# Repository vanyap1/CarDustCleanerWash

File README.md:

# CarDustCleanerWash
CarDustCleanerWash

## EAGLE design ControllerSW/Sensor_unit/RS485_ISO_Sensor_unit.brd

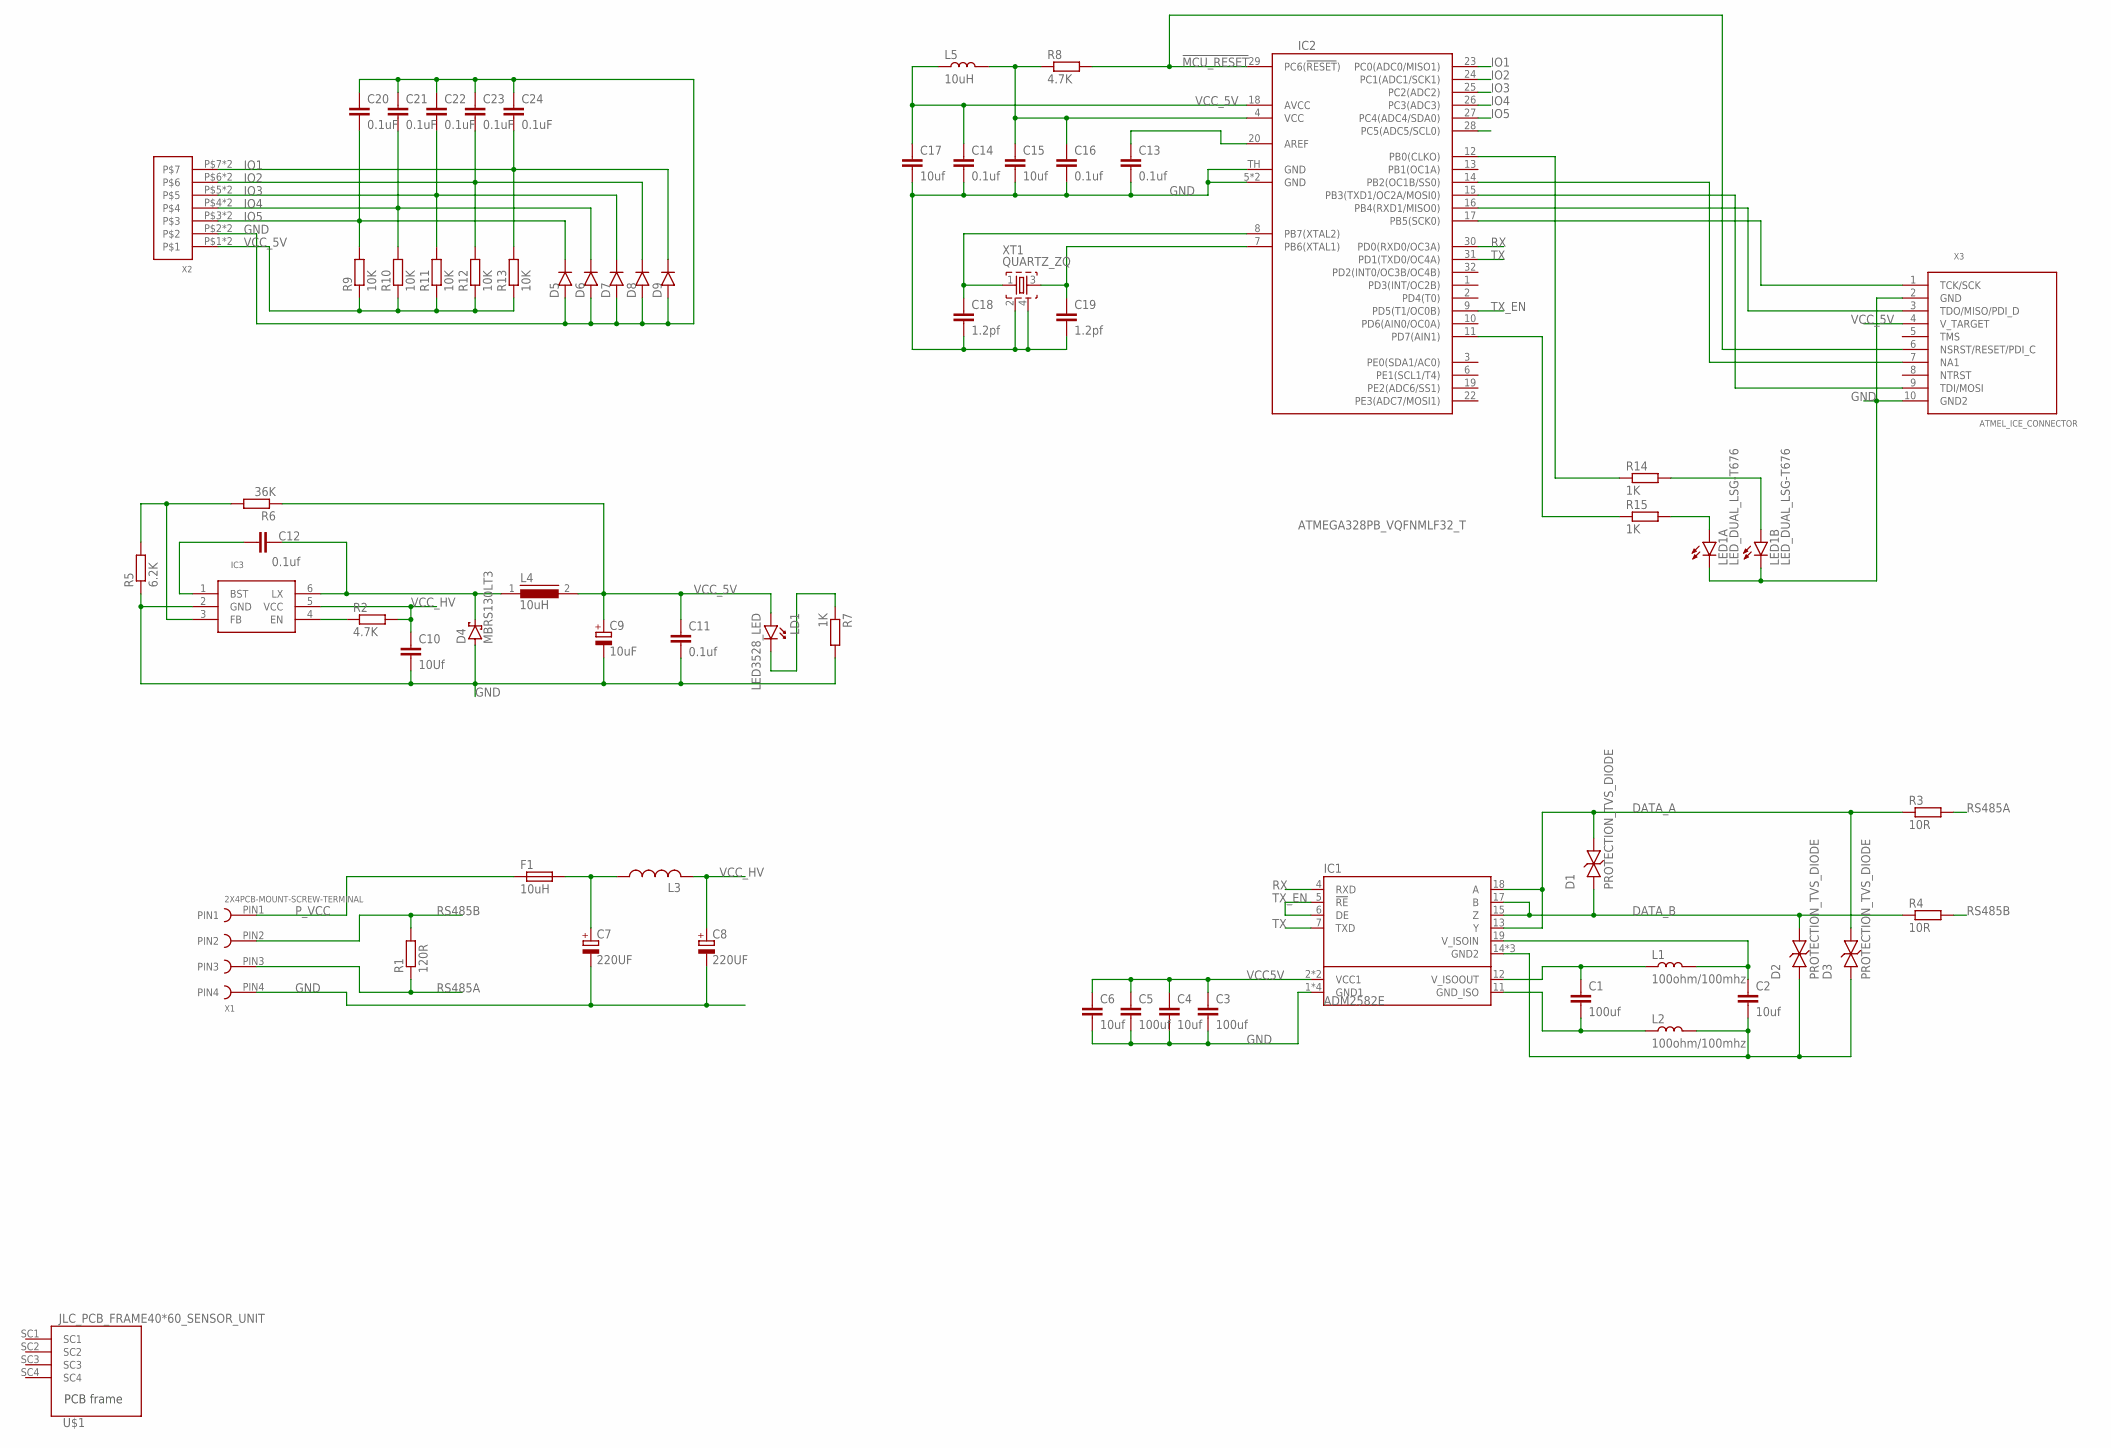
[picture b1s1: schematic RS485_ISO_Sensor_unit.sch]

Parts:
C1, C3, C5: 100uf; 0603
C2, C4, C6: 10uf; 0603
C7, C8: 220UF; 3.6MM
C9: 10uF; D/7343-31R
C10: 10Uf; 1206
C11, C12, C13, C14, C16: 0.1uf; 0603
C15, C17: 10uf; 3528
C18, C19: 1.2pf; 0603
C20, C21, C22, C23, C24: 0.1uF; 0603
D1, D2, D3: PROTECTION_TVS_DIODE; SMA403D
D4: MBRS130LT3; SMB
D5, D6, D7, D8, D9: L1N4148WT1GSOD123_GALILE0_SMALL; SOD-123_MINI-SMA
F1: 10uH; SMD_2410_FUSE_NOK
IC1: ADM2582E; SO20L
IC2: ATMEGA328PB_VQFNMLF32_T; MLF32-TH
IC3: BD9G101G_SOT23(6); SOT-23(6)
L1, L2: 100ohm/100mhz; 0805
L3: L-US0207/2V; 0207/2V
L4: 10uH; DR74
L5: 10uH; 0805
LD1: LED3528_LED; 3528
LED1: LED_DUAL_LSG-T676; P-LCC4-0
R1: 120R; 0204/5
R2, R8: 4.7K; 0603
R3, R4: 10R; 1206
R5: 6.2K; 0603
R6: 36K; 0603
R7, R14, R15: 1K; 0603
R9, R10, R11, R12, R13: 10K; 0603
U$1: JLC_PCB_FRAME40*60_SENSOR_UNIT; 40X60_SENSOR_UNIT
X1: 2X4PCB-MOUNT-SCREW-TERMINAL
X2: WAGO250_X7; WAGO250_FP_7X
X3: ATMEL_ICE_CONNECTOR; MINI10P_SPI/JTAG/PDI
XT1: QUARTZ_ZQ; QUARTZ_3X3MM

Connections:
!MCU_RESET: IC2.29 (PC6(!RESET!)), R8.2, X3.6 (NSRST/RESET/PDI_C)
AREF: C13.1, IC2.20 (AREF)
AVCC: C14.1, C17.M (1), IC2.18 (AVCC), L5.1
DATA_A: D1.P$2 (C), D3.P$2 (C), IC1.13 (Y), IC1.18 (A), R3.1
DATA_B: D1.P$1 (A), D2.P$2 (C), IC1.15 (Z), IC1.17 (B), R4.1
GND: C3.2, C4.2, C5.2, C6.2, C7.P$1 (-), C8.P$1 (-), C9.-, C10.2, C11.2, C13.2, C14.2, C15.P (2), C16.2, C17.P (2), C18.2, C19.2, C20.1, C21.1, C22.1, C23.1, C24.1, D4.A, D5.A, D6.A, D7.A, D8.A, D9.A, IC1.1 (GND1), IC1.3 (GND1), IC1.9 (GND1), IC1.10 (GND1), IC2.5 (GND), IC2.21 (GND), IC2.TH (GND), IC3.2 (GND), LED1.1 (C), LED1.3 (C), R5.1, R7.2, X1.PIN4, X2.P$2, X2.U$2, X3.2 (GND), X3.10 (GND2), XT1.2, XT1.4
GND2: C2.2, D2.P$1 (A), D3.P$1 (A), IC1.14 (GND2), IC1.16 (GND2), IC1.20 (GND2), L2.2
IO1: C24.2, D9.C, IC2.23 (PC0(ADC0/MISO1)), R13.2, X2.P$7, X2.U$7
IO2: C23.2, D8.C, IC2.24 (PC1(ADC1/SCK1)), R12.2, X2.P$6, X2.U$6
IO3: C22.2, D7.C, IC2.25 (PC2(ADC2)), R11.2, X2.P$5, X2.U$5
IO4: C21.2, D6.C, IC2.26 (PC3(ADC3)), R10.2, X2.P$4, X2.U$4
IO5: C20.2, D5.C, IC2.27 (PC4(ADC4/SDA0)), R9.2, X2.P$3, X2.U$3
unnamed: C7.P$2 (+), F1.P$2 (2), L3.1
unnamed: IC3.4 (EN), R2.1
unnamed: C1.1, IC1.12 (V_ISOOUT), L1.1
unnamed: C2.1, IC1.19 (V_ISOIN), L1.2
unnamed: C1.2, IC1.11 (GND_ISO), L2.1
unnamed: C12.1, IC3.1 (BST)
unnamed: IC3.3 (FB), R5.2, R6.2
unnamed: C12.2, D4.C, IC3.6 (LX), L4.1
unnamed: LED1.2 (A), R15.2
unnamed: LED1.4 (A), R14.2
unnamed: IC2.12 (PB0(CLKO)), R14.1
unnamed: LD1.M (K), R7.1
unnamed: IC2.17 (PB5(SCK0)), X3.1 (TCK/SCK)
unnamed: IC2.16 (PB4(RXD1/MISO0)), X3.3 (TDO/MISO/PDI_D)
unnamed: IC2.15 (PB3(TXD1/OC2A/MOSI0)), X3.9 (TDI/MOSI)
unnamed: IC2.11 (PD7(AIN1)), R15.1
unnamed: IC2.14 (PB2(OC1B/SS0)), X3.7 (NA1)
unnamed: C18.1, IC2.8 (PB7(XTAL2)), XT1.1
unnamed: C19.1, IC2.7 (PB6(XTAL1)), XT1.3
P_VCC: F1.P$1 (1), X1.PIN1
RS485A: R1.1, R3.2, X1.PIN3
RS485B: R1.2, R4.2, X1.PIN2
RX: IC1.4 (RXD), IC2.30 (PD0(RXD0/OC3A))
TX: IC1.7 (TXD), IC2.31 (PD1(TXD0/OC4A))
TX_EN: IC1.5 (!RE), IC1.6 (DE), IC2.9 (PD5(T1/OC0B))
VCC5V: C3.1, C4.1, C5.1, C6.1, IC1.2 (VCC1), IC1.8 (VCC1)
VCC_5V: C9.+, C11.1, C15.M (1), C16.1, IC2.4 (VCC), L4.2, L5.2, LD1.P (A), R6.1, R8.1, R9.1, R10.1, R11.1, R12.1, R13.1, X2.P$1, X2.U$1, X3.4 (V_TARGET)
VCC_HV: C8.P$2 (+), C10.1, IC3.5 (VCC), L3.2, R2.2

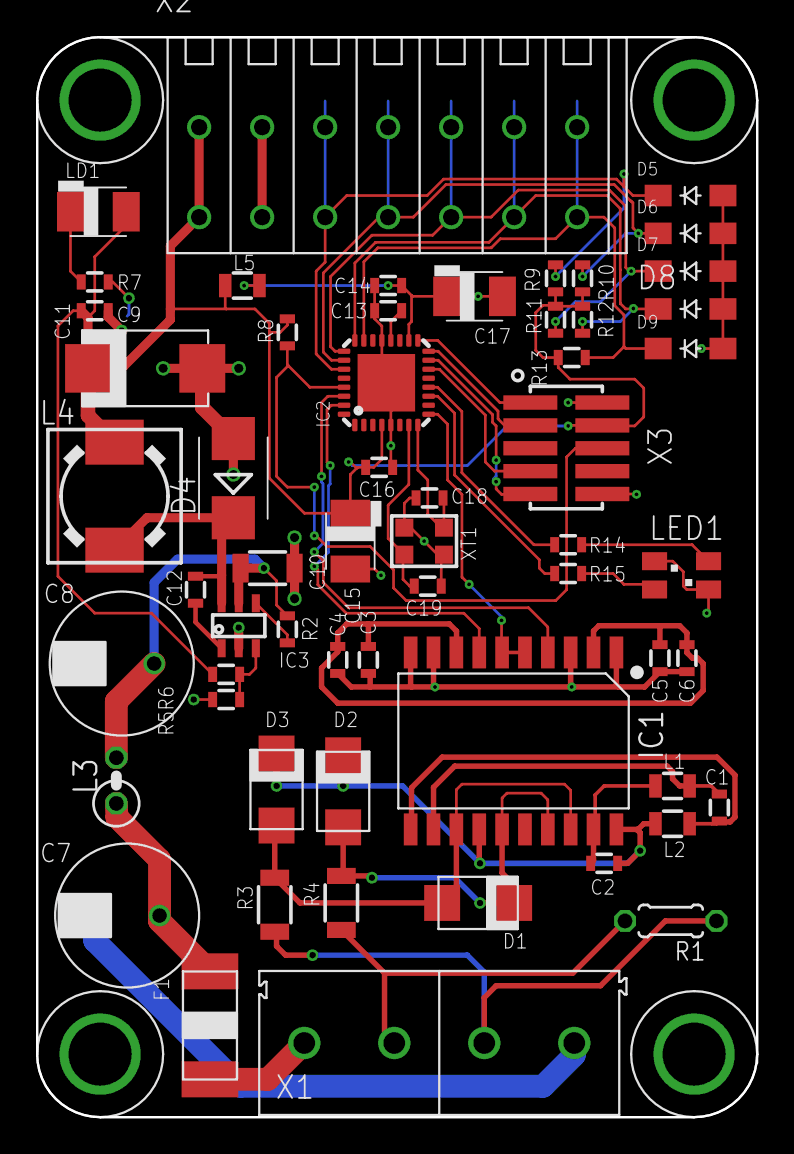
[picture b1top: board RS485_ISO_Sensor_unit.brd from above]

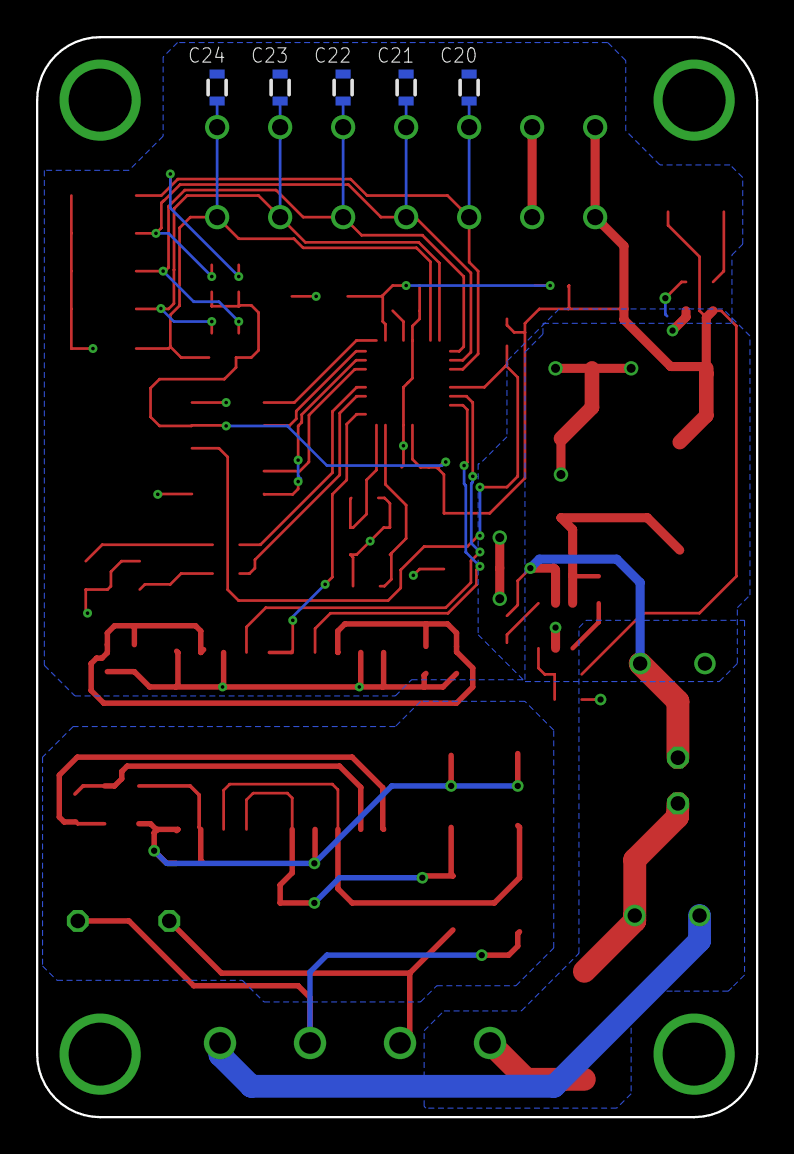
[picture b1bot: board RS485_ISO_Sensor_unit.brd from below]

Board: 2 copper layers, 40.0 x 60.0 mm, 64 parts (5 on the bottom side), 40 nets.

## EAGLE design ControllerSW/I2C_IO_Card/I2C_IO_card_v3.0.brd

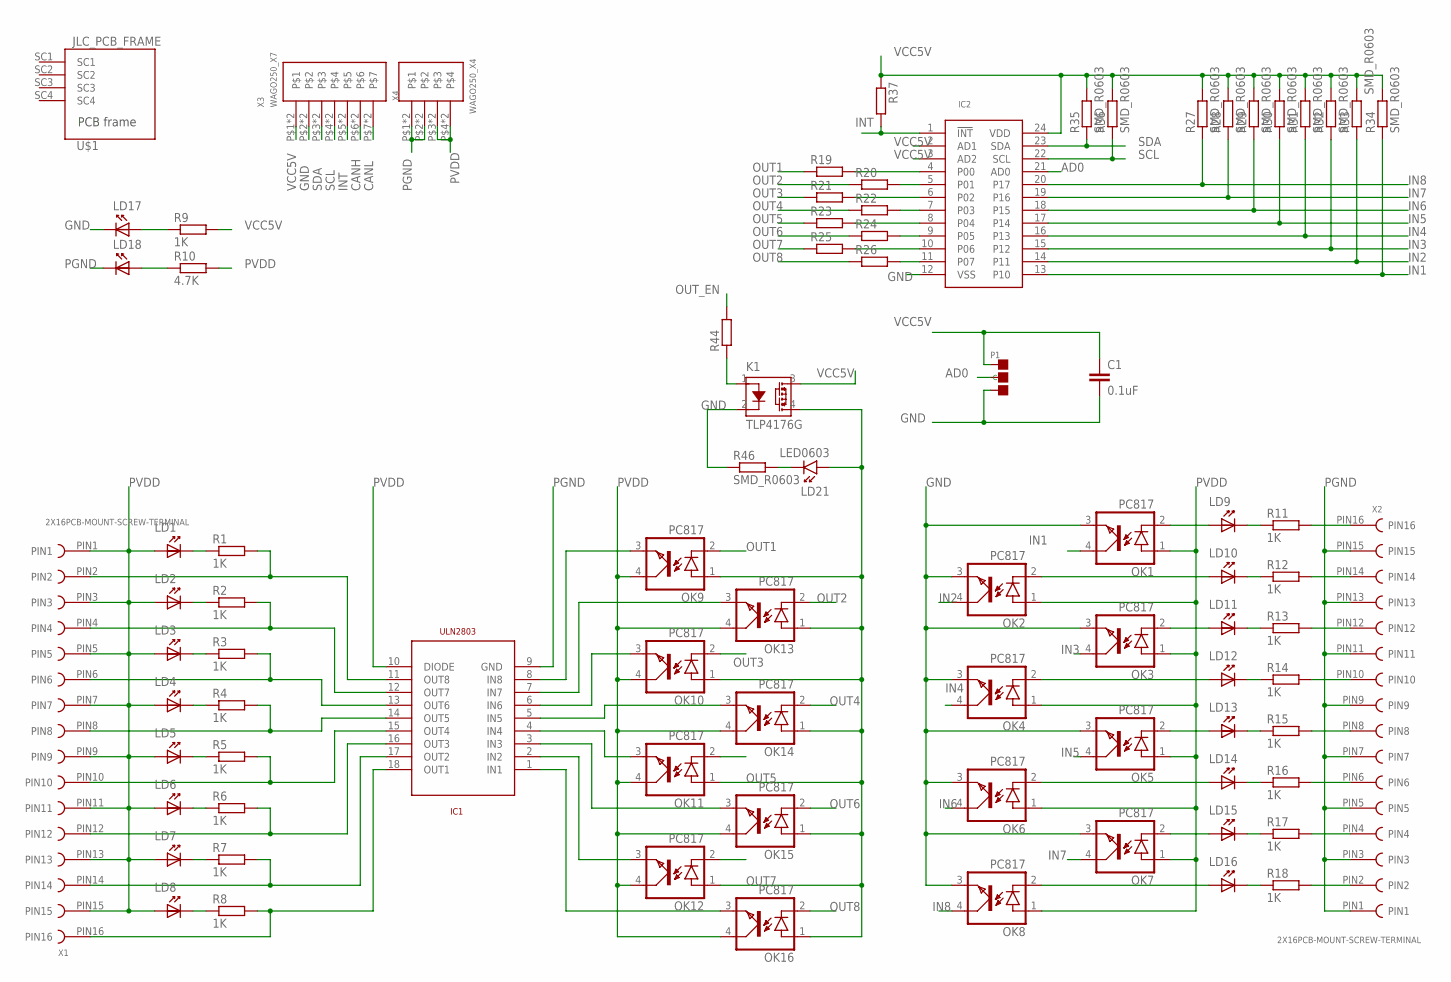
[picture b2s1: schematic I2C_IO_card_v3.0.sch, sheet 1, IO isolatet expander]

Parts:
C1: 0.1uF; C0603K
IC1: ULN2803; SO18L
IC2: PCA9675_TSSOP24; SOP65P640X110-24N
K1: TLP4176G; SOP04
LD1, LD2, LD3, LD4, LD5, LD6, LD7, LD8, LD9, LD10, LD11, LD12, LD13, LD14, LD15, LD16, LD17, LD18: LED; LED_RADIAL_3MM
LD21: LED0603; 0603_P
OK1, OK2, OK3, OK4, OK5, OK6, OK7, OK8, OK9, OK10, OK11, OK12, OK13, OK14, OK15, OK16: PC817; DIL04
P1: PAD-JUMPER-3P-40*40; 3P-SMD-4.1X1.5
R1, R2, R3, R4, R5, R6, R7, R8, R9, R11, R12, R13, R14, R15, R16, R17, R18: 1K; R0603
R10: 4.7K; R0603
R19, R20, R21, R22, R23, R24, R25, R26, R27, R28, R29, R30, R31, R32, R33, R34, R35, R36, R44, R46: SMD_R0603; 0603
R37: R-EU_RO603K; R0603K
U$1: JLC_PCB_FRAME; 80X100_PCB_FRAME
X1, X2: 2X16PCB-MOUNT-SCREW-TERMINAL
X3: WAGO250_X7; WAGO250_FP_7X
X4: WAGO250_X4; WAGO250_FP_4X

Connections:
AD0: IC2.21 (AD0), P1.MM (C)
CANH: X3.P$6, X3.U$6; also elsewhere on the board
CANL: X3.P$7, X3.U$7; also elsewhere on the board
GND: C1.2, IC2.12 (VSS), K1.2 (K), LD17.K, OK1.3 (EMIT), OK2.3 (EMIT), OK3.3 (EMIT), OK4.3 (EMIT), OK5.3 (EMIT), OK6.3 (EMIT), OK7.3 (EMIT), OK8.3 (EMIT), P1.11 (R), R46.1, X3.P$2, X3.U$2; also elsewhere on the board
IN1: IC2.13 (P10), OK1.4 (COL), R34.1; also elsewhere on the board
IN2: IC2.14 (P11), OK2.4 (COL), R33.1
IN3: IC2.15 (P12), OK3.4 (COL), R32.1
IN4: IC2.16 (P13), OK4.4 (COL), R31.1
IN5: IC2.17 (P14), OK5.4 (COL), R30.1
IN6: IC2.18 (P15), OK6.4 (COL), R29.1
IN7: IC2.19 (P16), OK7.4 (COL), R28.1
IN8: IC2.20 (P17), OK8.4 (COL), R27.1
INT: IC2.1 (!INT), R37.2, X3.P$5, X3.U$5; also elsewhere on the board
unnamed: LD1.K, R1.1
unnamed: LD2.K, R2.1
unnamed: LD3.K, R3.1
unnamed: LD4.K, R4.1
unnamed: LD5.K, R5.1
unnamed: LD6.K, R6.1
unnamed: LD7.K, R7.1
unnamed: LD8.K, R8.1
unnamed: IC1.18 (OUT1), R8.2, X1.PIN16
unnamed: IC1.17 (OUT2), R7.2, X1.PIN14
unnamed: IC1.16 (OUT3), R6.2, X1.PIN12
unnamed: IC1.15 (OUT4), R5.2, X1.PIN10
unnamed: IC1.14 (OUT5), R4.2, X1.PIN8
unnamed: IC1.13 (OUT6), R3.2, X1.PIN6
unnamed: IC1.12 (OUT7), R2.2, X1.PIN4
unnamed: IC1.11 (OUT8), R1.2, X1.PIN2
unnamed: LD17.A, R9.1
unnamed: LD18.A, R10.1
unnamed: R18.2, X2.PIN2
unnamed: R17.2, X2.PIN4
unnamed: R16.2, X2.PIN6
unnamed: R15.2, X2.PIN8
unnamed: R14.2, X2.PIN10
unnamed: R13.2, X2.PIN12
unnamed: R12.2, X2.PIN14
unnamed: R11.2, X2.PIN16
unnamed: LD9.K, R11.1
unnamed: LD10.K, R12.1
unnamed: LD11.K, R13.1
unnamed: LD12.K, R14.1
unnamed: LD13.K, R15.1
unnamed: LD14.K, R16.1
unnamed: LD15.K, R17.1
unnamed: LD16.K, R18.1
unnamed: LD9.A, OK1.2 (C)
unnamed: LD11.A, OK3.2 (C)
unnamed: LD13.A, OK5.2 (C)
unnamed: LD15.A, OK7.2 (C)
unnamed: LD16.A, OK8.2 (C)
unnamed: LD14.A, OK6.2 (C)
unnamed: LD12.A, OK4.2 (C)
unnamed: LD10.A, OK2.2 (C)
unnamed: IC2.4 (P00), R19.2
unnamed: IC1.8 (IN8), OK9.3 (EMIT)
unnamed: IC1.7 (IN7), OK13.3 (EMIT)
unnamed: IC1.6 (IN6), OK10.3 (EMIT)
unnamed: IC1.5 (IN5), OK14.3 (EMIT)
unnamed: IC1.4 (IN4), OK11.3 (EMIT)
unnamed: IC1.3 (IN3), OK15.3 (EMIT)
unnamed: IC1.2 (IN2), OK12.3 (EMIT)
unnamed: IC1.1 (IN1), OK16.3 (EMIT)
unnamed: IC2.5 (P01), R20.2
unnamed: IC2.6 (P02), R21.2
unnamed: IC2.7 (P03), R22.2
unnamed: IC2.8 (P04), R23.2
unnamed: IC2.9 (P05), R24.2
unnamed: IC2.10 (P06), R25.2
unnamed: IC2.11 (P07), R26.2
unnamed: K1.4 (DS2), LD21.2 (A), OK9.1 (A), OK10.1 (A), OK11.1 (A), OK12.1 (A), OK13.1 (A), OK14.1 (A), OK15.1 (A), OK16.1 (A)
unnamed: K1.1 (A), R44.1
unnamed: LD21.1 (K), R46.2
OUT1: OK9.2 (C), R19.1
OUT2: OK13.2 (C), R20.1
OUT3: OK10.2 (C), R21.1
OUT4: OK14.2 (C), R22.1
OUT5: OK11.2 (C), R23.1
OUT6: OK15.2 (C), R24.1
OUT7: OK12.2 (C), R25.1
OUT8: OK16.2 (C), R26.1
OUT_EN: R44.2; also elsewhere on the board
PGND: IC1.9 (GND), LD18.K, X2.PIN1, X2.PIN3, X2.PIN5, X2.PIN7, X2.PIN9, X2.PIN11, X2.PIN13, X2.PIN15, X4.P$1, X4.P$2, X4.U$1, X4.U$2; also elsewhere on the board
PVDD: IC1.10 (DIODE), LD1.A, LD2.A, LD3.A, LD4.A, LD5.A, LD6.A, LD7.A, LD8.A, OK1.1 (A), OK2.1 (A), OK3.1 (A), OK4.1 (A), OK5.1 (A), OK6.1 (A), OK7.1 (A), OK8.1 (A), OK9.4 (COL), OK10.4 (COL), OK11.4 (COL), OK12.4 (COL), OK13.4 (COL), OK14.4 (COL), OK15.4 (COL), OK16.4 (COL), R10.2, X1.PIN1, X1.PIN3, X1.PIN5, X1.PIN7, X1.PIN9, X1.PIN11, X1.PIN13, X1.PIN15, X4.P$3, X4.P$4, X4.U$3, X4.U$4; also elsewhere on the board
SCL: IC2.22 (SCL), R36.1, X3.P$4, X3.U$4; also elsewhere on the board
SDA: IC2.23 (SDA), R35.1, X3.P$3, X3.U$3; also elsewhere on the board
VCC5V: C1.1, IC2.2 (AD1), IC2.3 (AD2), IC2.24 (VDD), K1.3 (DS1), P1.00 (L), R9.2, R27.2, R28.2, R29.2, R30.2, R31.2, R32.2, R33.2, R34.2, R35.2, R36.2, R37.1, X3.P$1, X3.U$1; also elsewhere on the board

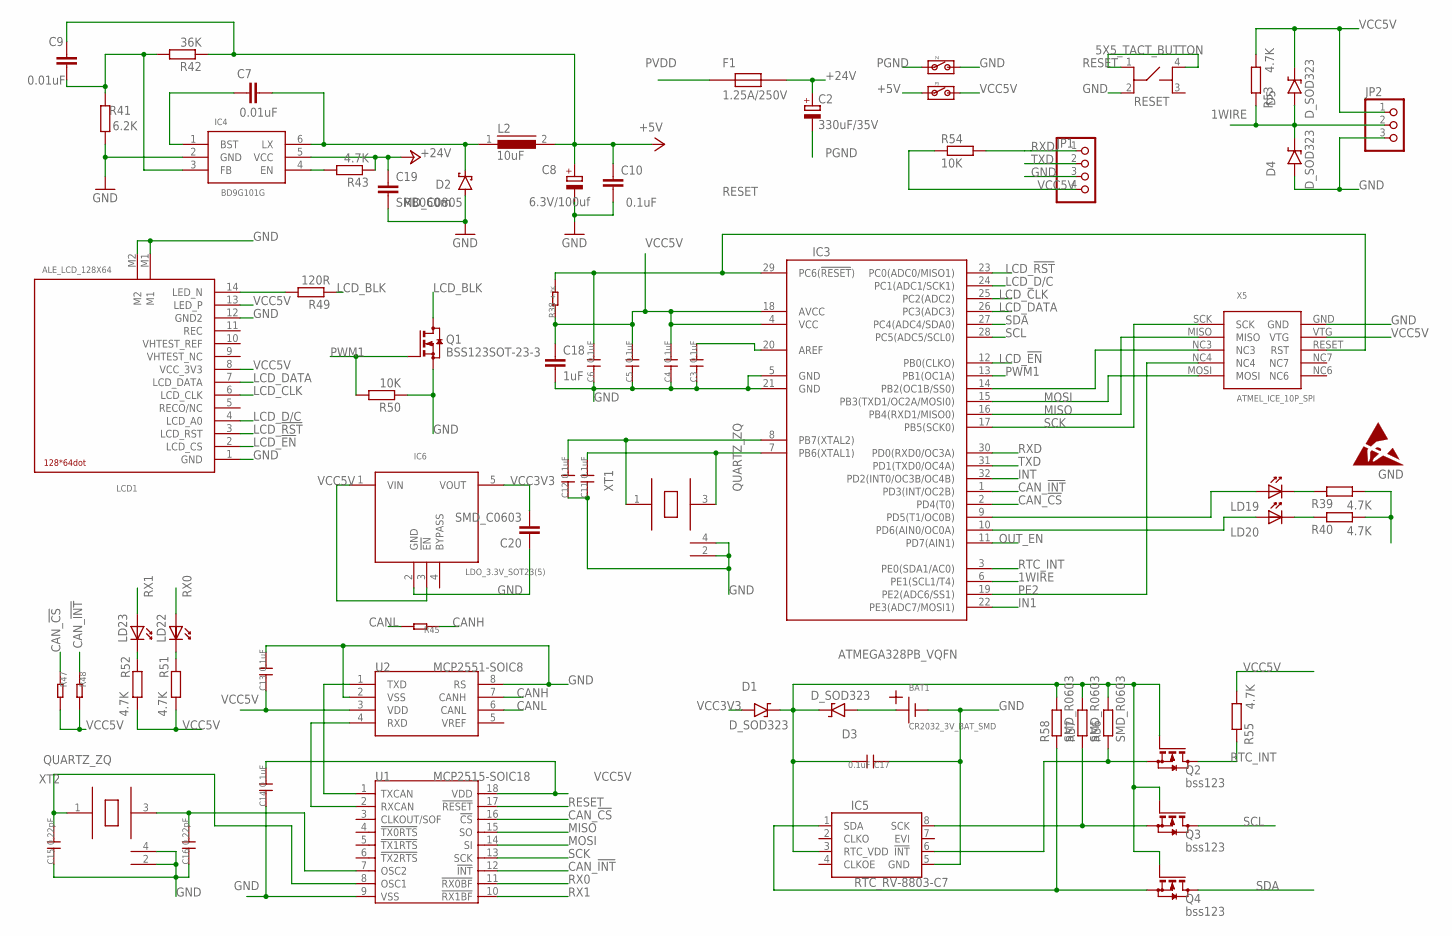
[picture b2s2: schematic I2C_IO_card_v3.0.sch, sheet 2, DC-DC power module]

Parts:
BAT1: CR2032_3V_BAT_SMD; CR2032_BAT
C2: 330uF/35V; E5-10,5
C3, C4, C5, C6, C10, C11, C12, C13, C14, C17: 0.1uF; 0603
C7, C9: 0.01uF; 0603
C8: 6.3V/100uf; 140CLH-0810
C15, C16: 0.22pF; 0603
C18: 1uF; C1206K
C19: SMD_C0805; 0805
C20: SMD_C0603; 0603
D1, D3, D4, D5: D_SOD323; SOD-323_D
D2: RB060m; SMB
F1: 1.25A/250V; FUSE_DIP_2.5A250V
IC3: ATMEGA328PB_VQFN; MLF32
IC4: BD9G101G; SOT-23(6)
IC5: RTC_RV-8803-C7; C7_RTC
IC6: LDO_3.3V_SOT23(5); SOT-23(5)
JP1: PINHD-1X4; 1X04
JP2: PINHD-1X3; 1X03
L2: 10uF; DR74
LCD1: ALE_LCD_128X64; ALE_LCD_14PIN_CONNECTOR
LD19, LD20, LD22, LD23: LEDLED_SMD_0603; D0603K
P4, P5: PAD-JUMPER-2P; 2P-SMD-1.78X1.27
Q1: BSS123SOT-23-3; SOT-23(3)
Q2, Q3, Q4: bss123; SOT-23(3)
R38, R43, R55: 4.7K; 0603
R39, R40, R51, R52, R53: 4.7K; R0603K
R41: 6.2K; 0603
R42: 36K; 0603
R45, R47, R48: R-0603; 0603
R49: 120R; 0603
R50, R54: 10K; 0603
R56, R57, R58: SMD_R0603; 0603
RESET: 5X5_TACT_BUTTON; 5X5_4PIN_TACT_BUTTON
U1: MCP2515-SOIC18; SOIC18
U2: MCP2551-SOIC8; SOIC8-6.0
X5: ATMEL_ICE_10P_SPI; ATMEL_ISP_2X5PIN_SMD
XT1, XT2: QUARTZ_ZQ; QUARTZ_3X3MM

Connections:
1WIRE: D4.K, D5.A, IC3.6 (PE1(SCL1/T4)), JP2.2, R53.2
+5V: C8.+, C9.2, C10.2, L2.2, P5.1, R42.1
+24V: C2.+, C19.1, F1.P$2, IC4.5 (VCC), R43.1
CANH: R45.1, U2.7 (CANH); also elsewhere on the board
CANL: R45.2, U2.6 (CANL); also elsewhere on the board
CAN_!CS: IC3.2 (PD4(T0)), R47.1, U1.16 (!CS)
CAN_!INT: IC3.1 (PD3(INT/OC2B)), R48.1, U1.12 (!INT)
GND: BAT1.P$2 (-), C3.1, C4.1, C5.1, C6.1, C11.1, C12.1, C13.2, C14.1, C15.1, C16.1, C17.1, C18.2, C20.1, D4.A, IC3.5 (GND), IC3.21 (GND), IC5.5 (GND), IC6.2 (GND), JP1.3, JP2.3, LCD1.1 (GND), LCD1.12 (GND2), LCD1.M1, LCD1.M2, P4.2, Q1.2 (S), R39.1, R40.1, R50.1, RESET.2, U1.9 (VSS), U2.2 (VSS), U2.8 (RS), X5.GND, XT1.2 (GND1), XT1.4 (GND2), XT2.2 (GND1), XT2.4 (GND2); also elsewhere on the board
IN1: IC3.22 (PE3(ADC7/MOSI1)); also elsewhere on the board
INT: IC3.32 (PD2(INT0/OC3B/OC4B)); also elsewhere on the board
LCD_!EN: IC3.12 (PB0(CLKO)), LCD1.2 (LCD_CS)
LCD_!RST: IC3.23 (PC0(ADC0/MISO1)), LCD1.3 (LCD_RST)
LCD_BLK: Q1.3 (D), R49.1
LCD_CLK: IC3.25 (PC2(ADC2)), LCD1.6 (LCD_CLK)
LCD_D/C: IC3.24 (PC1(ADC1/SCK1)), LCD1.4 (LCD_A0)
LCD_DATA: IC3.26 (PC3(ADC3)), LCD1.7 (LCD_DATA)
MISO: IC3.16 (PB4(RXD1/MISO0)), U1.15 (SO), X5.MISO
MOSI: IC3.15 (PB3(TXD1/OC2A/MOSI0)), U1.14 (SI), X5.MOSI
unnamed: LCD1.14 (LED_N), R49.2
unnamed: C3.2, IC3.20 (AREF)
unnamed: C17.2, D1.K, D3.K, IC5.3 (RTC_VDD), Q2.1 (G), Q3.1 (G), Q4.1 (G), R56.2, R57.2, R58.2
unnamed: BAT1.P$1 (+), D3.A
unnamed: C7.1, IC4.1 (BST)
unnamed: C7.2, D2.C, IC4.6 (LX), L2.1
unnamed: C9.1, IC4.3 (FB), R41.2, R42.2
unnamed: IC4.4 (EN), R43.2
unnamed: LD19.K- (K), R39.2
unnamed: C12.2, IC3.8 (PB7(XTAL2)), XT1.1
unnamed: C11.2, IC3.7 (PB6(XTAL1)), XT1.3 (2)
unnamed: IC3.14 (PB2(OC1B/SS0)), X5.NC3
unnamed: LD20.K- (K), R40.2
unnamed: U1.1 (TXCAN), U2.1 (TXD)
unnamed: IC3.10 (PD6(AIN0/OC0A)), LD20.A+ (A)
unnamed: IC3.9 (PD5(T1/OC0B)), LD19.A+ (A)
unnamed: U1.2 (RXCAN), U2.4 (RXD)
unnamed: IC5.1 (SDA), Q4.2 (S), R58.1
unnamed: C16.2, U1.7 (OSC2), XT2.3 (2)
unnamed: C15.2, U1.8 (OSC1), XT2.1
unnamed: LD22.K- (K), R51.2
unnamed: LD23.K- (K), R52.2
unnamed: IC5.8 (SCK), Q3.2 (S), R57.1
unnamed: IC5.6 (!INT), Q2.2 (S), R56.1
OUT_EN: IC3.11 (PD7(AIN1)); also elsewhere on the board
PE2: IC3.19 (PE2(ADC6/SS1)), X5.NC4
PGND: C2.-, C8.-, C10.1, C19.2, D2.A, IC4.2 (GND), P4.1, R41.1; also elsewhere on the board
PVDD: F1.P$1; also elsewhere on the board
PWM1: IC3.13 (PB1(OC1A)), Q1.1 (G), R50.2
RESET: C6.2, IC3.29 (PC6(!RESET!)), R38.2, RESET.1, RESET.4, U1.17 (!RESET), X5.RESET (RST)
RTC_INT: IC3.3 (PE0(SDA1/AC0)), Q2.3 (D), R55.2
RX0: LD22.A+ (A), U1.11 (!RX0BF)
RX1: LD23.A+ (A), U1.10 (!RX1BF)
RXD: IC3.30 (PD0(RXD0/OC3A)), JP1.1, R54.2
SCK: IC3.17 (PB5(SCK0)), U1.13 (SCK), X5.SCK
SCL: IC3.28 (PC5(ADC5/SCL0)), Q3.3 (D); also elsewhere on the board
SDA: IC3.27 (PC4(ADC4/SDA0)), Q4.3 (D); also elsewhere on the board
TXD: IC3.31 (PD1(TXD0/OC4A)), JP1.2
VCC3V3: C20.2, D1.A, IC6.5 (VOUT)
VCC5V: C4.2, C5.2, C13.1, C14.2, C18.1, D5.K, IC3.4 (VCC), IC3.18 (AVCC), IC6.1 (VIN), IC6.3 (!EN!), JP1.4, JP2.1, LCD1.8 (VCC_3V3), LCD1.13 (LED_P), P5.2, R38.1, R47.2, R48.2, R51.1, R52.1, R53.1, R54.1, R55.1, U1.18 (VDD), U2.3 (VDD), X5.VTG; also elsewhere on the board

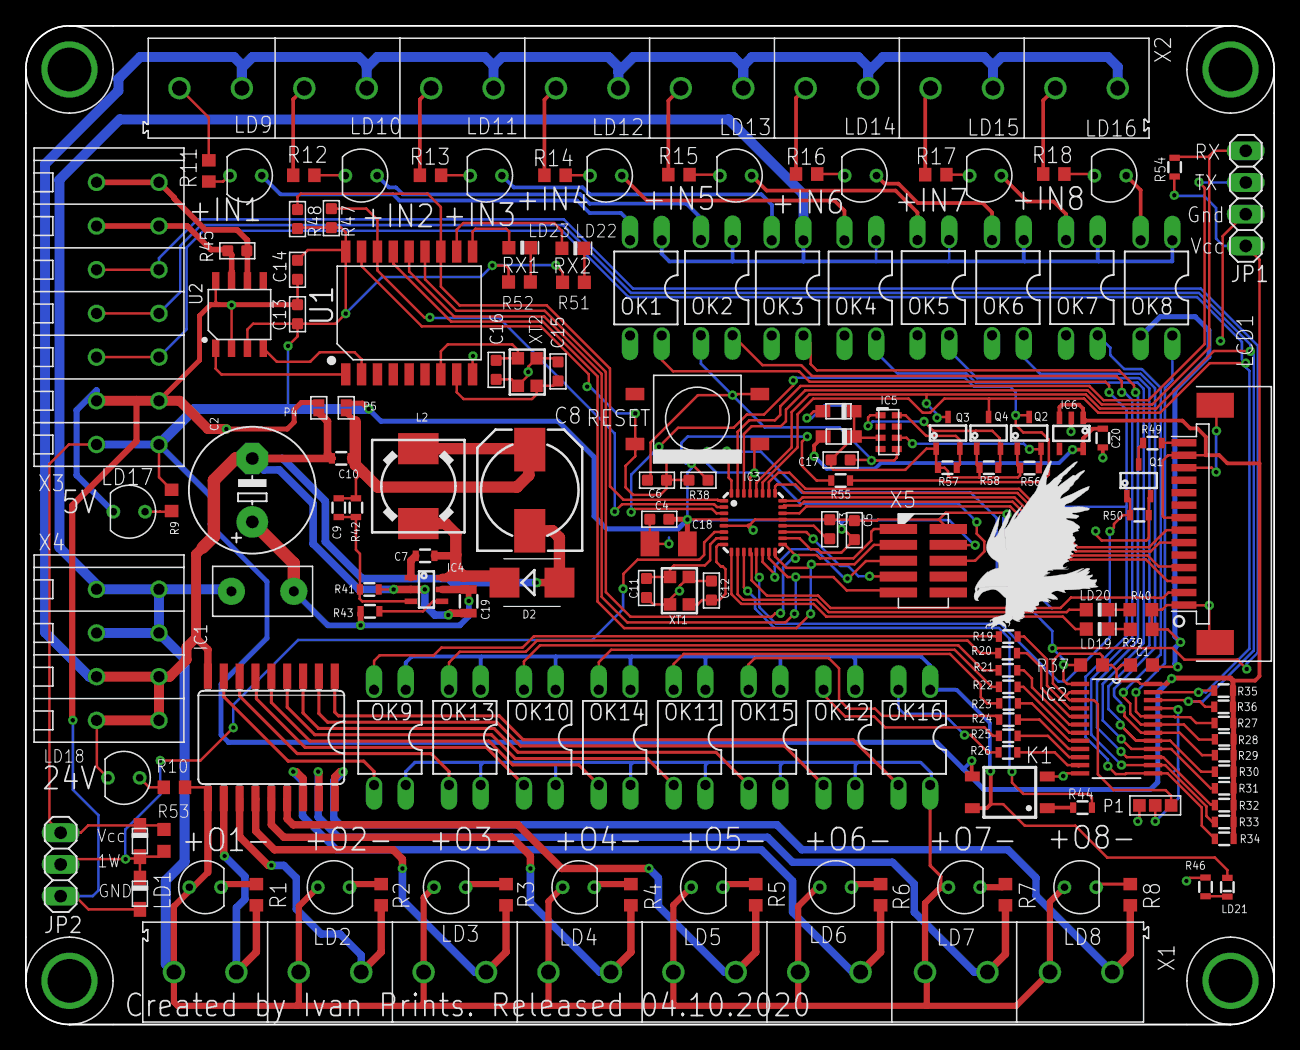
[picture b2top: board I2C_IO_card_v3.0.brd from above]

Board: 2 copper layers, 100.0 x 80.0 mm, 154 parts (1 on the bottom side), 135 nets.

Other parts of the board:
U$3: EAGLE-PLC-10MM

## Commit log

2025-05-05 HW docs update
2025-05-07 schematic update
